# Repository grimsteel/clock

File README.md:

# Clock

> Working 4-person location clock. Uses Home Assistant location zone information.

## Usage

### Assembly

1. 3D-print and laser cut the necessary components (see the `cad/` folder for a parts list and Onshape link)
2. Solder the ESP32 and pin headers onto the PCB.
3. Assemble the back frame (back, PCB, standoffs, and servo mount)
4. Attach the servos to the servo mount
5. Add the shafts, placing PTFE washers in between
6. Attach the front frame
7. Attach the front decorations and the hands

### Using it

8. Install one of the provided firmwares, configuring the people/locations as necessary (see `firmware/README.md`)
9. Profit. This does rely on accurate zone information in Home Assistant.

## Technical Information

### Structure

More information can be found in the `cad/` folder. The clock consists of a laser cut front and back frame.

Each hand is controlled by a servo with a 2:1 gear ratio. The servos and gears are mouted on a 3d-printed frame, which is fastened to the back frame.

The hands are attached to four concentric shafs, each terminating at a different height. This is part of the reason the clock is so thick.

The front includes 4 possible mounting spots for LEDs.

### PCB

The PCB consists of a surface mounted ESP32 C3 Supermini with connections for the 4 servos and 2 LEDs:

| Schematic                               | 3D render                      |
|-----------------------------------------|--------------------------------|
|  |   |
| Front                                   | Back                           |
|          |  |

### Firmware

Two firmwares are provided: an ESPHome and a native ESP-IDF firmware. More information can be found in the `firmware/` folder.

## BOM

| Description                | Link                                                       | Per-unit price | Quantity | Total price | Running price w/ tax |
|----------------------------|------------------------------------------------------------|----------------|----------|-------------|----------------------|
| CAD components             | https://cad.onshape.com/documents/5b8ef3e45edb03dc1124a4e9 | $0.00          | 1        | $0.00       | $0.00                |
| PCB                        | https://oshpark.com                                        | $6.45          | 1        | $6.45       | $7.01                |
| ESP32-C3 Supermini         | https://www.aliexpress.us/item/3256807292829704.html       | $2.70          | 1        | $2.70       | $9.94                |
| MG90s Micro Servo (5 pack) | https://www.aliexpress.us/item/3256808303872992.html       | $9.88          | 1        | $9.88       | $20.68               |

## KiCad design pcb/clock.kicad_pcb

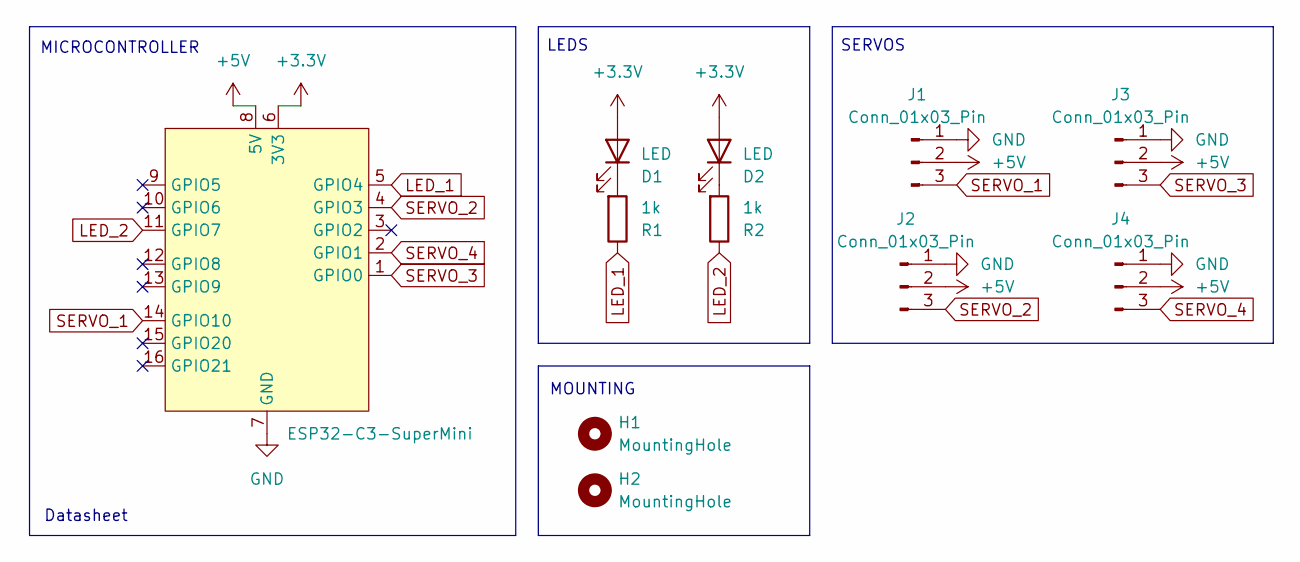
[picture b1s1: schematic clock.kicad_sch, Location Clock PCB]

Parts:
D1, D2: LED; SolderWire-0.5sqmm_1x02_P4.6mm_D0.9mm_OD2.1mm
H1, H2: MountingHole; MountingHole_3.2mm_M3
J1, J2, J3, J4: Conn_01x03_Pin; PinHeader_1x03_P2.54mm_Vertical
R1, R2: 1k; R_Axial_DIN0204_L3.6mm_D1.6mm_P7.62mm_Horizontal
U1: ESP32-C3-SuperMini

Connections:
+3.3V: D1.2 (A), D2.2 (A), U1.6 (3V3)
+5V: J1.2, J2.2, J3.2, J4.2, U1.8 (5V)
GND: J1.1, J2.1, J3.1, J4.1, U1.7 (GND)
LED_1: R1.1, U1.5 (GPIO4)
LED_2: R2.1, U1.11 (GPIO7)
unnamed: D1.1 (K), R1.2
unnamed: D2.1 (K), R2.2
SERVO_1: J1.3, U1.14 (GPIO10)
SERVO_2: J2.3, U1.4 (GPIO3)
SERVO_3: J3.3, U1.1 (GPIO0)
SERVO_4: J4.3, U1.2 (GPIO1)

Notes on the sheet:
MOUNTING
MICROCONTROLLER
LEDS
Datasheet
SERVOS

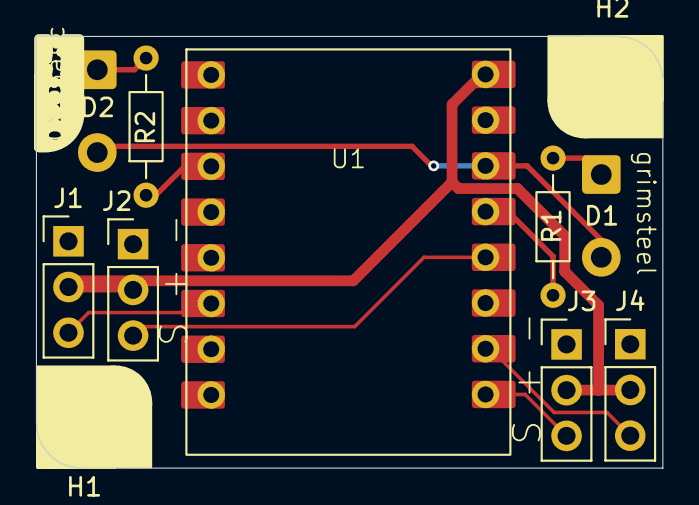
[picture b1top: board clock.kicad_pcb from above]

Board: 2 copper layers, 34.8 x 24.0 mm, 11 parts (0 on the bottom side), 11 nets.

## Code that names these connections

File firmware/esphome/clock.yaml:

# ESPHome base config

esphome:
  name: presence_clock
  friendly_name: Presence Clock
  includes:
    - location_mappings.h

esp32:
  variant: esp32c3
  framework:
    type: esp-idf

logger:

api:
  encryption:
    key: ""

ota:
  - platform: esphome
    password: ""

wifi:
  ssid: !secret wifi_ssid
  password: !secret wifi_password
  domain: ".local"
  use_address: ""

  ap:
    ssid: "Clock Fallback Hotspot"
    password: ""

captive_portal:

# Clock-specific config

text_sensor:
  - platform: homeassistant
    id: person_1
    entity_id: person.person_1
    on_value:
      then:
        - script.execute: apply_locations
  - platform: homeassistant
    id: person_2
    entity_id: person.person_2
    on_value:
      then:
        - script.execute: apply_locations
  - platform: homeassistant
    id: person_3
    entity_id: person.person_3
    on_value:
      then:
        - script.execute: apply_locations
  - platform: homeassistant
    id: person_4
    entity_id: person.person_4
    on_value:
      then:
        - script.execute: apply_locations

output:
  # LEDs
  - platform: gpio
    pin: GPIO4
    id: light_left
    inverted: true
  - platform: gpio
    pin: GPIO7
    id: light_right
    inverted: true
  # Servos
  - platform: ledc
    pin: GPIO10
    frequency: "50Hz"
    id: servo_out_1
  - platform: ledc
    pin: GPIO3
    frequency: "50Hz"
    id: servo_out_2
  - platform: ledc
    pin: GPIO0
    frequency: "50Hz"
    id: servo_out_3
  - platform: ledc
    pin: GPIO1
    frequency: "50Hz"
    id: servo_out_4

light:
  - platform: status_led
    name: "Onboard LED"
    pin:
      number: GPIO8
      inverted: true
  - platform: binary
    output: light_left
    name: "Left LED"
  - platform: binary
    output: light_right
    name: "Right LED"

servo:
  - id: servo_1
    output: servo_out_1
  - id: servo_2
    output: servo_out_2
  - id: servo_3
    output: servo_out_3
  - id: servo_4
    output: servo_out_4

script:
  - id: apply_locations
    # if a location update happens while this is running, just restart the script
    mode: restart
    then:
      - lambda: |-
          string loc_states_str[] = {
            id(person_1).state,
            id(person_2).state,
            id(person_3).state,
            id(person_4).state
          };
          int loc_states[4];
          double servo_states[4];
          // parse location string into int (see external header file)
          for (int i = 0; i < 4; i++) loc_states[i] = location_int(loc_states_str[i]);
          
          int sector_size = 360 / 5; // 5 locs
          // each hand has its own subsector to avoid overlap
          int subsector_size = sector_size / 4;
          
          for (int i = 0; i < 4; i++) {
             // convert [0, 5) to [0, 360)
             loc_states[i] *= sector_size;
             // hand offset
             loc_states[i] += subsector_size * i;
             // put in middle
             loc_states[i] += subsector_size / 2;
             // map to [-1, 1]
             servo_states[i] = (loc_states[i] - 180) / 180.0;
          }
          id(servo_1).write(servo_states[0]);
          id(servo_2).write(servo_states[1]);
          id(servo_3).write(servo_states[2]);
          id(servo_4).write(servo_states[3]);
          

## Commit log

2026-03-24 cad: initial complete clock cad
2026-03-29 pcb: finish v1 schematic, pcb
2026-04-04 pcb: led improvements
2026-04-04 firmware: add esphome firmware
2026-04-06 firmware: add initial native firmware
2026-04-06 native firmware: finish Wi-Fi
2026-04-12 finish native firmware: mqtt, servos, event loop
2026-04-13 docs: finish readme, add screenshots and prod files
2026-04-22 bom: update links
2026-04-28 pcb: remove jlc serial
